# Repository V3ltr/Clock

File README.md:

# Matrix Clock

So this is my matrix clock. It must be connected to a power suply to run, i find my computer to be the best. It has a 8x32 matrix led display thats controlled by a separate controller, the main microcontroller is the esp32 DEVKITC. It has a alarm function:  you press the button one and then use the knob to set the time.l you turn left for hours and right for minutes. After setting the time you press the button to arm it. After it is armed you can press the button for the third time to cancel the alarm.
When the alarm finishes the screen flashes for 60s.

Part	Qty	Unit	Total	Vendor	Link
PCB	1	$17.47	$17.47	JLCPCB	https://cart.jlcpcb.com/shopcart/cart/
Rotary encoder	1	$1.33	$1.33	Dratek	https://dratek.cz/arduino-platforma/837-rotacni-enkoder.html
Led Matrix 8x32	1	$6.33	$6.33	Dratek	https://dratek.cz/arduino-platforma/5009-led-matice-4x64-s-kontrolerem-max7219.html
ESP32 DEVKITC	1	$11.37	$11.37	Dratek	https://dratek.cz/arduino-platforma/232741-vyvojova-deska-esp32-devkitc-38pin-usb-c.html

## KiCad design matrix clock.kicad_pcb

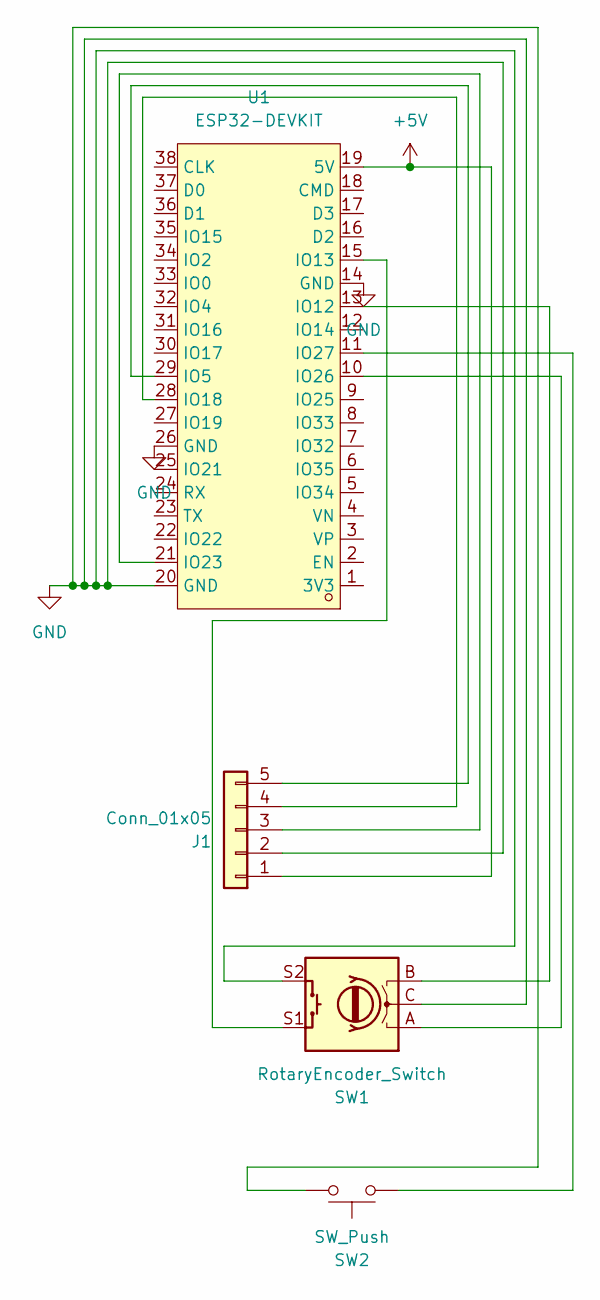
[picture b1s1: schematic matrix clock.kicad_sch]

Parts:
J1: Conn_01x05; PinSocket_1x05_P2.54mm_Vertical
SW1: RotaryEncoder_Switch; RotaryEncoder_Alps_EC11E-Switch_Vertical_H20mm
SW2: SW_Push; SW_Cherry_MX_1.00u_PCB
U1: ESP32-DEVKIT; BULETM-SMD_ESP32-DEVKITC(1); MPN ESP32-DevKitC; LCSC Part C571180

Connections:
+5V: J1.1, U1.19 (5V)
GND: J1.2, SW1.C, SW1.S2, SW2.2, U1.14 (GND), U1.20 (GND), U1.26 (GND)
unnamed: J1.3, U1.21 (IO23)
unnamed: J1.4, U1.28 (IO18)
unnamed: J1.5, U1.29 (IO5)
unnamed: SW1.B, U1.13 (IO12)
unnamed: SW1.S1, U1.15 (IO13)
unnamed: SW1.A, U1.10 (IO26)
unnamed: SW2.1, U1.11 (IO27)

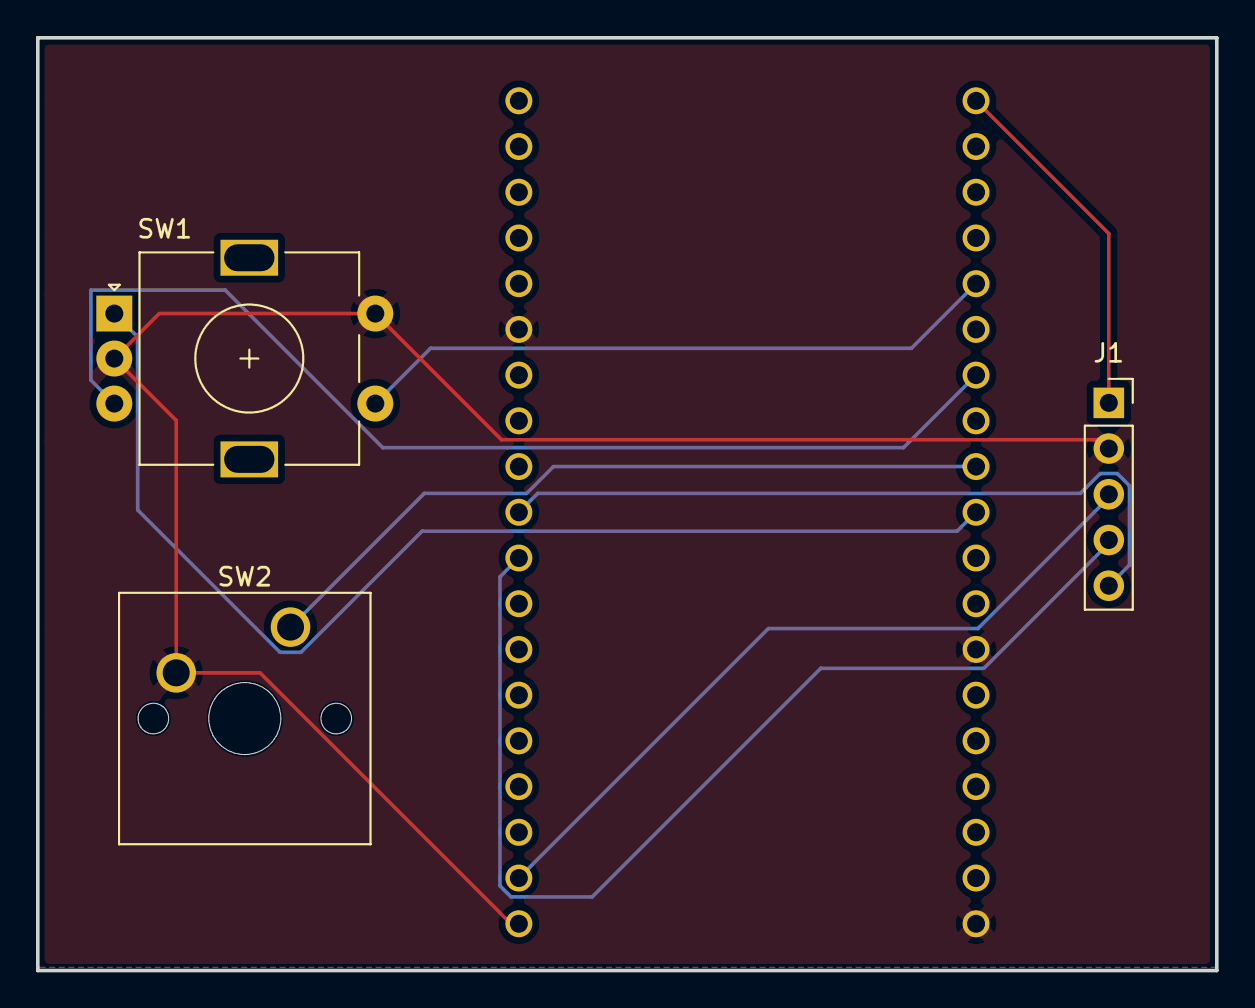
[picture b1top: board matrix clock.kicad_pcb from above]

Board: 2 copper layers, 65.5 x 51.8 mm, 4 parts (1 on the bottom side), 9 nets.
